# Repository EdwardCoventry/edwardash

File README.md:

# edwardash
a 30+6 key version of omkb's ergodash

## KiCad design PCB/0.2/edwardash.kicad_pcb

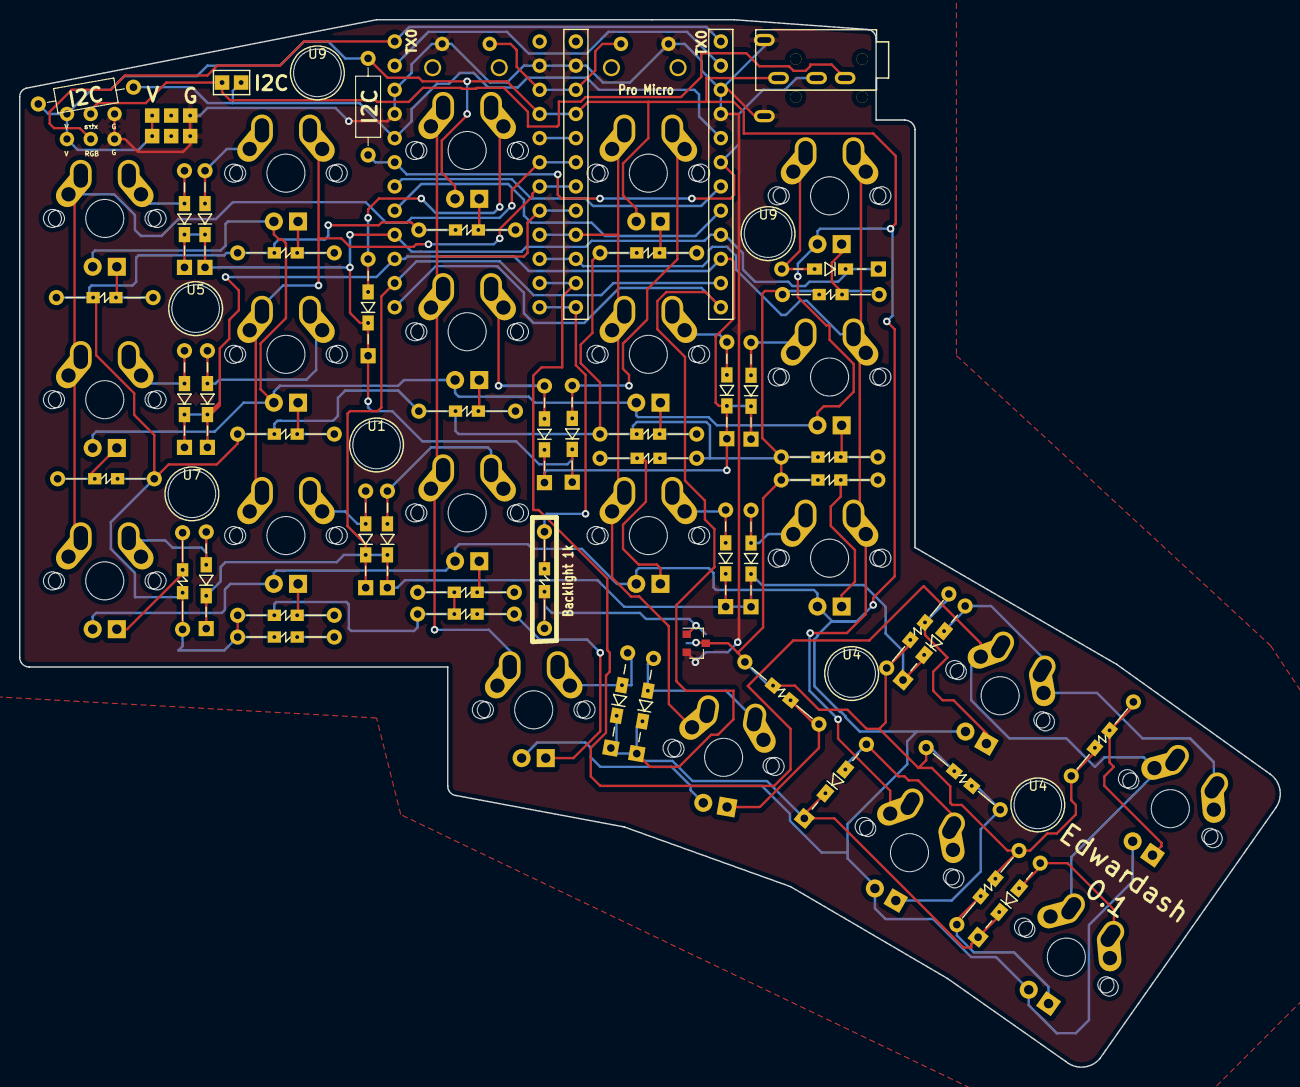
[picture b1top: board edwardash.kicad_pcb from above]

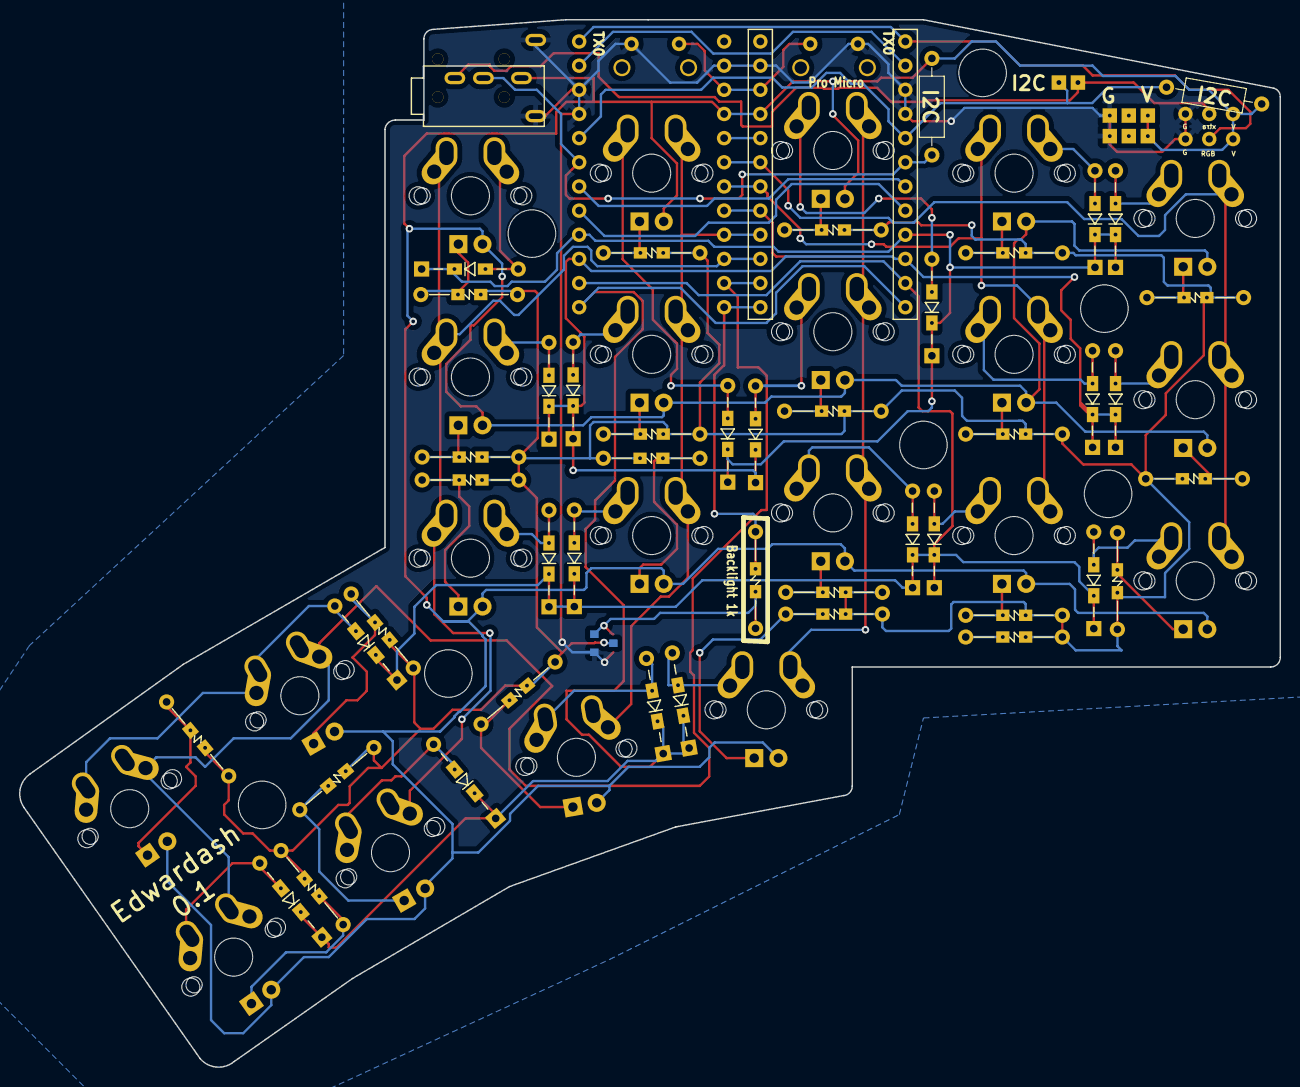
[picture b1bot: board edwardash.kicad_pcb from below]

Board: 2 copper layers, 132.5 x 110.1 mm, 104 parts (6 on the bottom side), 65 nets.

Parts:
D6, D7, D8, D10, D11, D12, D14, D15, D16, D18, D19, D20, D22, D23, D24, D28, D32, D33, D34, D68: D; Diode_SMD_THT3
D43, D44, D45, D46, D47, D50, D51, D52, D53, D54, D57, D58, D59, D60, D61, D62, D67, D69, D70, D71, D72: LED; CHERRY_MX_LED2
J1: 5PIN; trrs_jack
J2: Conn_01x03; conn3
J4, J5: GS3; jumper2
Q1: IRLML6344TRPbF; SOT-23_2
R1, R2: R; R_Axial_DIN0207_L6.3mm_D2.5mm_P10.16mm_Horizontal
R11, R12, R14, R15, R16, R17, R20, R21, R22, R23, R24, R27, R28, R29, R30, R31, R32, R35, R36, R37, R38, R39: R; Resistors_SMD_THT
R13: 1k; Resistors_SMD_THT
SW6, SW7, SW8, SW10, SW11, SW12, SW14, SW15, SW16, SW18, SW19, SW20, SW22, SW23, SW24, SW28, SW34, SW35, SW38, SW39, SW41: SW_PUSH; MX_ALPS
SW29, SW37: SW_Push; tact_switch2
U1, U4, U4#2, U5, U7, U9, U9#2: HOLE; hole
U3, U6: ProMicro; ProMicro_rev
W1: jumper_smd; jumper_smd_2dub

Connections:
/Audio: U3.8, U6.8
/Backlight: R13.1, U3.13, U6.13
/RBG: J2.2, U3.1, U6.1
/RX: U3.2, U6.2
/col0: U3.20, U6.20
/col1: SW6.1, SW7.1, SW8.1, U3.19, U6.19
/col2: SW10.1, SW11.1, SW12.1, U3.18, U6.18
/col3: SW14.1, SW15.1, SW16.1, SW38.1, U3.17, U6.17
/col4: SW18.1, SW19.1, SW20.1, SW34.1, U3.16, U6.16
/col5: SW22.1, SW23.1, SW24.1, SW35.1, U3.15, U6.15
/col6: SW28.1, SW39.1, SW41.1, U3.14, U6.14
/row0: U3.7, U6.7
/row1: D6.1, D10.1, D14.1, D18.1, D22.1, U3.9, U6.9
/row2: D7.1, D11.1, D15.1, D19.1, D23.1, U3.10, U6.10
/row3: D8.1, D12.1, D16.1, D20.1, D24.1, D28.1, U3.11, U6.11
/row4: D32.1, D33.1, D34.1, D68.1, U3.12, U6.12
/rst: SW29.1, SW37.1, U3.22, U6.22
/scl: R1.2, U3.5, U6.5, W1.2
/sda/uart: J1.3, R2.2, U3.6, U6.6
/xtradata: J1.2, W1.1
GND: J1.4, J1.5, J2.3, J4.3, J5.3, Q1.2, SW29.2, SW37.2, U3.3, U3.4, U3.23, U6.3, U6.4, U6.23
unnamed: D6.2, SW6.2
unnamed: D7.2, SW7.2
unnamed: D8.2, SW8.2
unnamed: D10.2, SW10.2
unnamed: D11.2, SW11.2
unnamed: D12.2, SW12.2
unnamed: D14.2, SW14.2
unnamed: D15.2, SW15.2
unnamed: D16.2, SW16.2
unnamed: D18.2, SW18.2
unnamed: D19.2, SW19.2
unnamed: D20.2, SW20.2
unnamed: D22.2, SW22.2
unnamed: D23.2, SW23.2
unnamed: D24.2, SW24.2
unnamed: D28.2, SW28.2, SW39.2
unnamed: D32.2, SW38.2
unnamed: D33.2, SW34.2
unnamed: D34.2, SW35.2
unnamed: D43.1, R11.1
unnamed: D44.1, R12.1
unnamed: D45.1, R15.1
unnamed: D46.1, R16.1
unnamed: D47.1, R17.1
unnamed: D50.1, R20.1
unnamed: D51.1, R21.1
unnamed: D52.1, R22.1
unnamed: D53.1, R23.1
unnamed: D54.1, R24.1
unnamed: D57.1, R27.1
unnamed: D58.1, R28.1
unnamed: D59.1, R29.1
unnamed: D60.1, R30.1
unnamed: D61.1, R31.1
unnamed: D62.1, R32.1
unnamed: D67.1, R36.1
unnamed: D68.2, SW41.2
unnamed: D69.1, R14.1
unnamed: D70.1, R37.1
unnamed: D71.1, R38.1
unnamed: D72.1, R39.1
unnamed: Q1.1, R13.2
unnamed: Q1.3, R11.2, R12.2, R14.2, R15.2, R16.2, R17.2, R20.2, R21.2, R22.2, R23.2, R24.2, R27.2, R28.2, R29.2, R30.2, R31.2, R32.2, R35.2, R36.2, R37.2, R38.2, R39.2
VCC: D43.2, D44.2, D45.2, D46.2, D47.2, D50.2, D51.2, D52.2, D53.2, D54.2, D57.2, D58.2, D59.2, D60.2, D61.2, D62.2, D67.2, D69.2, D70.2, D71.2, D72.2, J1.1, J2.1, J4.1, J5.1, R1.1, R2.1, U3.21, U6.21

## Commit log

2023-08-18 first build
2023-08-18 added fusion files
2023-11-20 breaking changes
